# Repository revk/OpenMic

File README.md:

# OpenMic

Now at [Codeberg](https://codeberg.org/RevK/ESP32-OpenMic)

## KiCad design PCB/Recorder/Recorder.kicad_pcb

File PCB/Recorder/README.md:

# Recorder

These files are for use in [KiCad](https://www.kicad.org).

## Trademark

This is an open source project, but bear in mind you cannot sell boards bearing the Andrews & Arnold Ltd name, the A&A logo, the registered trademark AJK logo, or the GS1 allocated EANs assigned to Andrews & Arnold Ltd.

## Images

*Auto generated 2025-08-10T16:03:46*

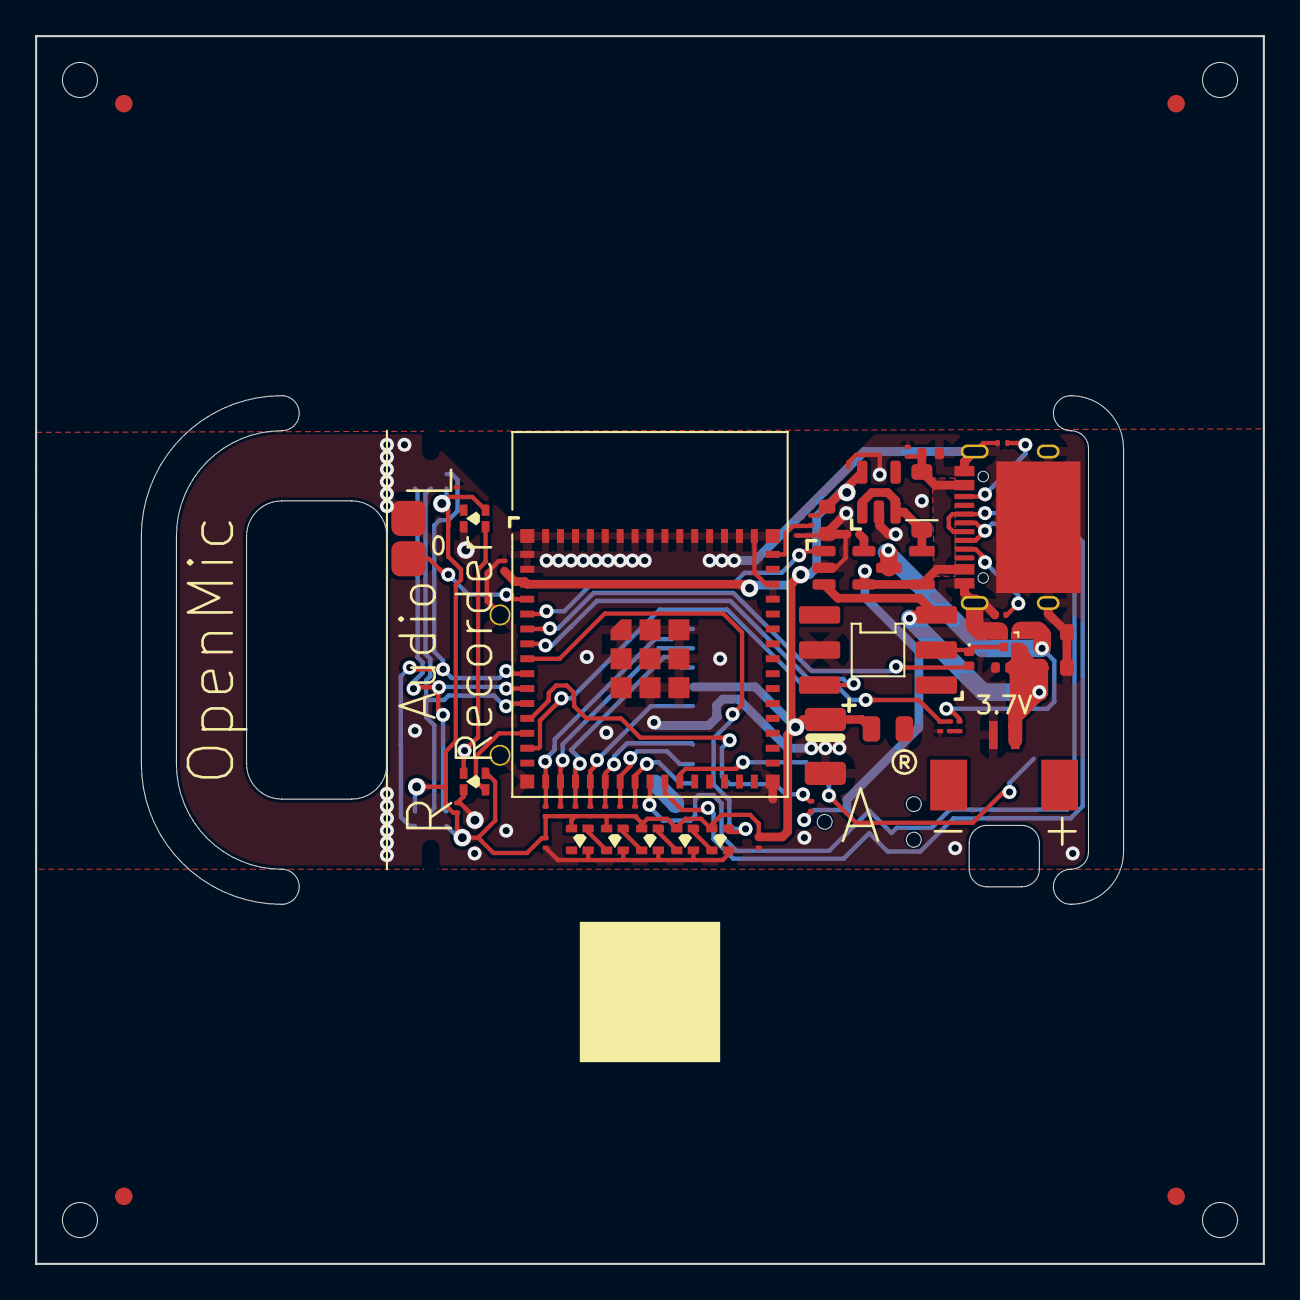
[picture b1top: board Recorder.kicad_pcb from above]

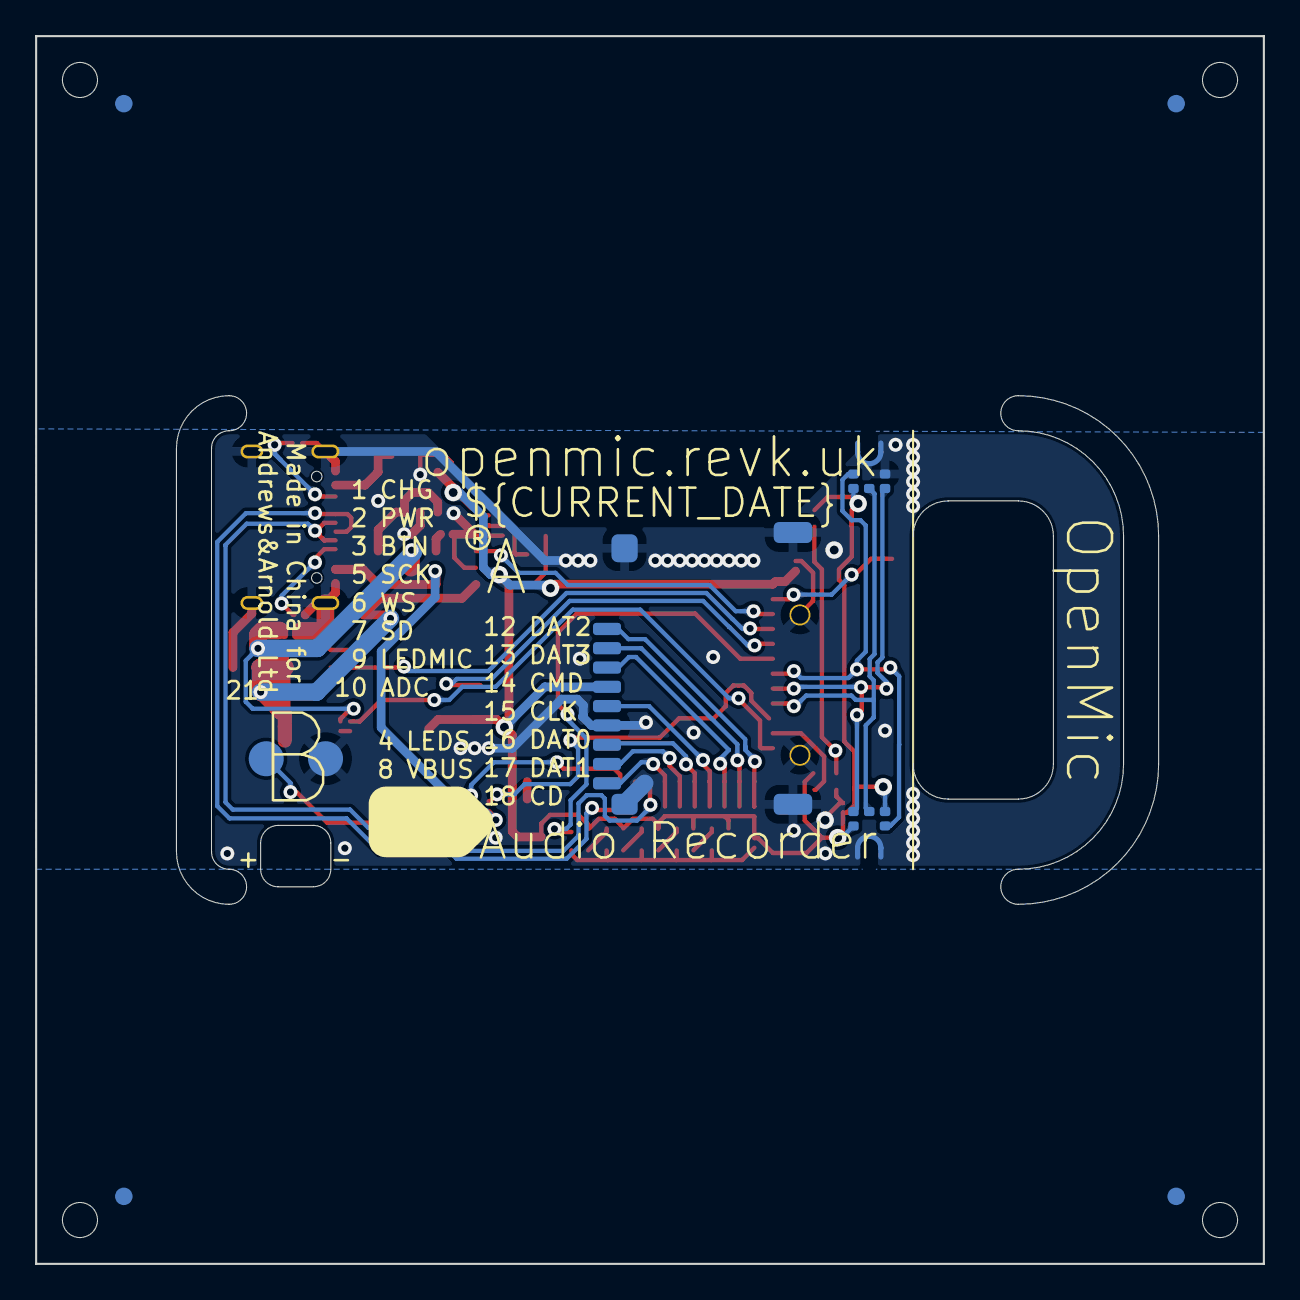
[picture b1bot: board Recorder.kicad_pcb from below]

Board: 2 copper layers, 70.0 x 70.0 mm, 57 parts (7 on the bottom side), 38 nets.

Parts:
BT1: Battery; LiPo1
C1, C3, C5: 22uF; C_0603
C2: 1uF; C_0201
C4, C10, C11, C12, C14: 100nF; C_0201
C6: 220uF Tant; CP_EIA-3528-21_Kemet-B
C7: 10uF 6.3V; C_0402
C9: 100uF; C_0805
D1: D; D_0402
D2: DFN1006-2L
D3: MBR0530; D_SOD-123
D4, D5, D6, D7, D8, D9, D10: XL-1010RGBC-WS2812B; SMD1615
J1: Reset; AA-Pad
J3: TC2030-USB-NL-DS; Tag-Connect_TC2030-IDC-NL_2x03_P1.27mm_Vertical
J4: TF_PUSH
J5: USB-C-Socket-H
J6: Battery; 1.25T-2PWT (Molex 532610271)
PCB1: 70x70; PCB7070
Q1: CJ2301; SOT-23
R1, R2, R3, R4, R5, R6, R7, R9, R10, R11: 10K; R_0201
R8, R12, R13: 5K1; R_0201
R14, R15, R16: 100K 1%; R_0201
SW1: SW_Push_DPDT
TP1, TP2: TestPoint; PAD-2mm
U1: ESP32-S3-MINI-1-N4R2; ESP32-S3-MINI-1
U2: TPS22916CNYFPR; WCSP-4-0.78x0.78
U3: TP4054; SOT-23-5
U4: ME6211C33M5G-N; SOT-23-5-90
U5, U6: ICS-43434; ICS43434_MEMS_Mic_Open
V1, V2: VCUT70N

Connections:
+3V3: C4.1, C5.1, C6.1, C9.1, C10.2, C11.2, C12.1, C14.1, D4.3 (+), D5.3 (+), D6.3 (+), D7.3 (+), D8.3 (+), D9.3 (+), D10.3 (+), J4.4 (VDD), R2.1, R3.1, R4.1, R5.1, R6.1, R7.1, R9.1, R10.1, U1.3 (3V3), U4.5 (OUT), U5.5 (VDD), U6.2 (LR), U6.5 (VDD)
ADC: R15.2, R16.1, U1.14 (GPIO10)
BLINK: D4.2 (I), U1.8 (GPIO4)
BTN: SW1.4 (C), U1.7 (GPIO3)
CHARGING: U1.5 (GPIO1), U3.1 (STAT)
D+: J3.4 (D+), J5.A6 (D+), J5.B6 (D+), U1.24 (GPIO20)
D-: J3.2 (NC), J3.3 (D-), J3.6 (NC), J5.A7 (D-), J5.B7 (D-), U1.23 (GPIO19)
GND: C1.2, C2.2, C3.2, C4.2, C5.2, C6.2, C7.2, C9.2, C10.1, C11.1, C12.2, C14.2, D2.1, D4.1 (-), D5.1 (-), D6.1 (-), D7.1 (-), D8.1 (-), D9.1 (-), D10.1 (-), J1.1, J3.5 (GND), J4.6 (VSS), J4.S (SHIELD), J5.A1 (GND), J5.A12 (GND), J5.B1 (GND), J5.B12 (GND), J5.S1 (SHIELD), J6.2, R8.1, R11.2, R12.2, R13.1, R16.2, SW1.5 (B), TP2.1, U1.1 (GND), U1.2 (GND), U1.42 (GND), U1.43 (GND), U1.46 (GND), U1.47 (GND), U1.48 (GND), U1.49 (GND), U1.50 (GND), U1.51 (GND), U1.52 (GND), U1.53 (GND), U1.54 (GND), U1.55 (GND), U1.56 (GND), U1.57 (GND), U1.58 (GND), U1.59 (GND), U1.60 (GND), U1.61 (GND), U1.62 (GND), U1.63 (GND), U1.64 (GND), U1.65 (GND), U2.B1 (GND), U3.2 (VSS), U4.2 (GND), U5.2 (LR), U5.3 (GND), U6.3 (GND)
LEDMIC: D7.2 (I), U1.13 (GPIO9)
unnamed: D1.1 (K), SW1.2 (B), U2.B2 (ON)
unnamed: D3.1 (K), Q1.2 (S), U4.1 (IN), U4.3 (EN)
unnamed: D4.4 (O), D5.2 (I)
unnamed: D5.4 (O), D6.2 (I)
unnamed: D6.4 (O), D8.2 (I)
unnamed: D7.4 (O), D9.2 (I)
unnamed: D8.4 (O), D10.2 (I)
unnamed: J1.2, U1.25 (GPIO21)
unnamed: J5.A5 (CC1), R12.1
unnamed: J5.B5 (CC2), R13.2
unnamed: R14.2, R15.1
unnamed: C2.1, R2.2, U1.45 (EN)
unnamed: TP1.1, U1.4 (GPIO0)
unnamed: R1.1, U1.12 (GPIO8)
unnamed: R8.2, U3.5 (PROG)
PWR: D1.2 (A), U1.6 (GPIO2)
SCK: U1.9 (GPIO5), U5.4 (SCK), U6.4 (SCK)
SD: U1.11 (GPIO7), U5.6 (SD), U6.6 (SD)
SDCD: J4.9 (CD), R3.2, U1.22 (GPIO18)
SDCLK: J4.5 (CLK), R6.2, U1.19 (GPIO15)
SDCMD: J4.3 (CMD), R7.2, U1.18 (GPIO14)
SDDAT0: J4.7 (DAT0), R5.2, U1.20 (GPIO16)
SDDAT1: J4.8 (DAT1), R4.2, U1.21 (GPIO17)
SDDAT2: J4.1 (DAT2), R10.2, U1.16 (GPIO12)
SDDAT3: J4.2 (DAT3/CD), R9.2, U1.17 (GPIO13)
VBATCHG: C1.1, D2.2, J6.1, SW1.3 (C), U2.A2 (VIN), U3.3 (VBAT)
VBUS: C7.1, D3.2 (A), J3.1 (VBUS), J5.A4 (VBUS), J5.A9 (VBUS), J5.B4 (VBUS), J5.B9 (VBUS), Q1.1 (G), R1.2, R11.1, U3.4 (VDD)
VSWITCHED: C3.1, Q1.3 (D), R14.1, U2.A1 (VOUT)
WS: U1.10 (GPIO6), U5.1 (WS), U6.1 (WS)

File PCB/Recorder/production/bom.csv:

Designator,Footprint,Quantity,Value,LCSC Part #
"C1, C3, C5",C_0603,3,22uF,
"C10, C11, C12, C14, C4",C_0201,5,100nF,
C2,C_0201,1,1uF,
C6,CP_EIA-3528-21_Kemet-B,1,220uF Tant,C122649
C7,C_0402,1,10uF 6.3V,C15525
C9,C_0805,1,100uF,C141660
D1,D_0402,1,D,C28642302
"D10, D4, D5, D6, D7, D8, D9",SMD1615,7,XL-1010RGBC-WS2812B,C5349954
D2,DFN1006-2L,1,~,C5137770
D3,D_SOD-123,1,MBR0530,C5204746
J4,TF_PUSH,1,TF_PUSH,C393941
J5,USB-C-Socket-H,1,USB-C-Socket-H,C709357
J6,1.25T-2PWT (Molex 532610271),1,Battery,C177225
Q1,SOT-23,1,CJ2301,C8547
"R1, R10, R11, R2, R3, R4, R5, R6, R7, R9",R_0201,10,10K,C106225
"R12, R13, R8",R_0201,3,5K1,C274341
"R14, R15, R16",R_0201,3,100K 1%,C717003
SW1,SW_Push_DPDT,1,SW_Push_DPDT,C2911139
U1,ESP32-S3-MINI-1,1,ESP32-S3-MINI-1-N4R2,C3013941
U2,WCSP-4-0.78x0.78,1,TPS22916CNYFPR,C2655476
U3,SOT-23-5,1,TP4054,C668215
U4,SOT-23-5-90,1,ME6211C33M5G-N,
"U5, U6",ICS43434_MEMS_Mic_Open,2,ICS-43434,C5656610

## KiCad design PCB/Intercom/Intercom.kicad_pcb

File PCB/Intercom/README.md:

# Intercom

These files are for use in [KiCad](https://www.kicad.org).

## Trademark

This is an open source project, but bear in mind you cannot sell boards bearing the Andrews & Arnold Ltd name, the A&A logo, the registered trademark AJK logo, or the GS1 allocated EANs assigned to Andrews & Arnold Ltd.

## Images

*Auto generated 2025-08-10T15:43:51*

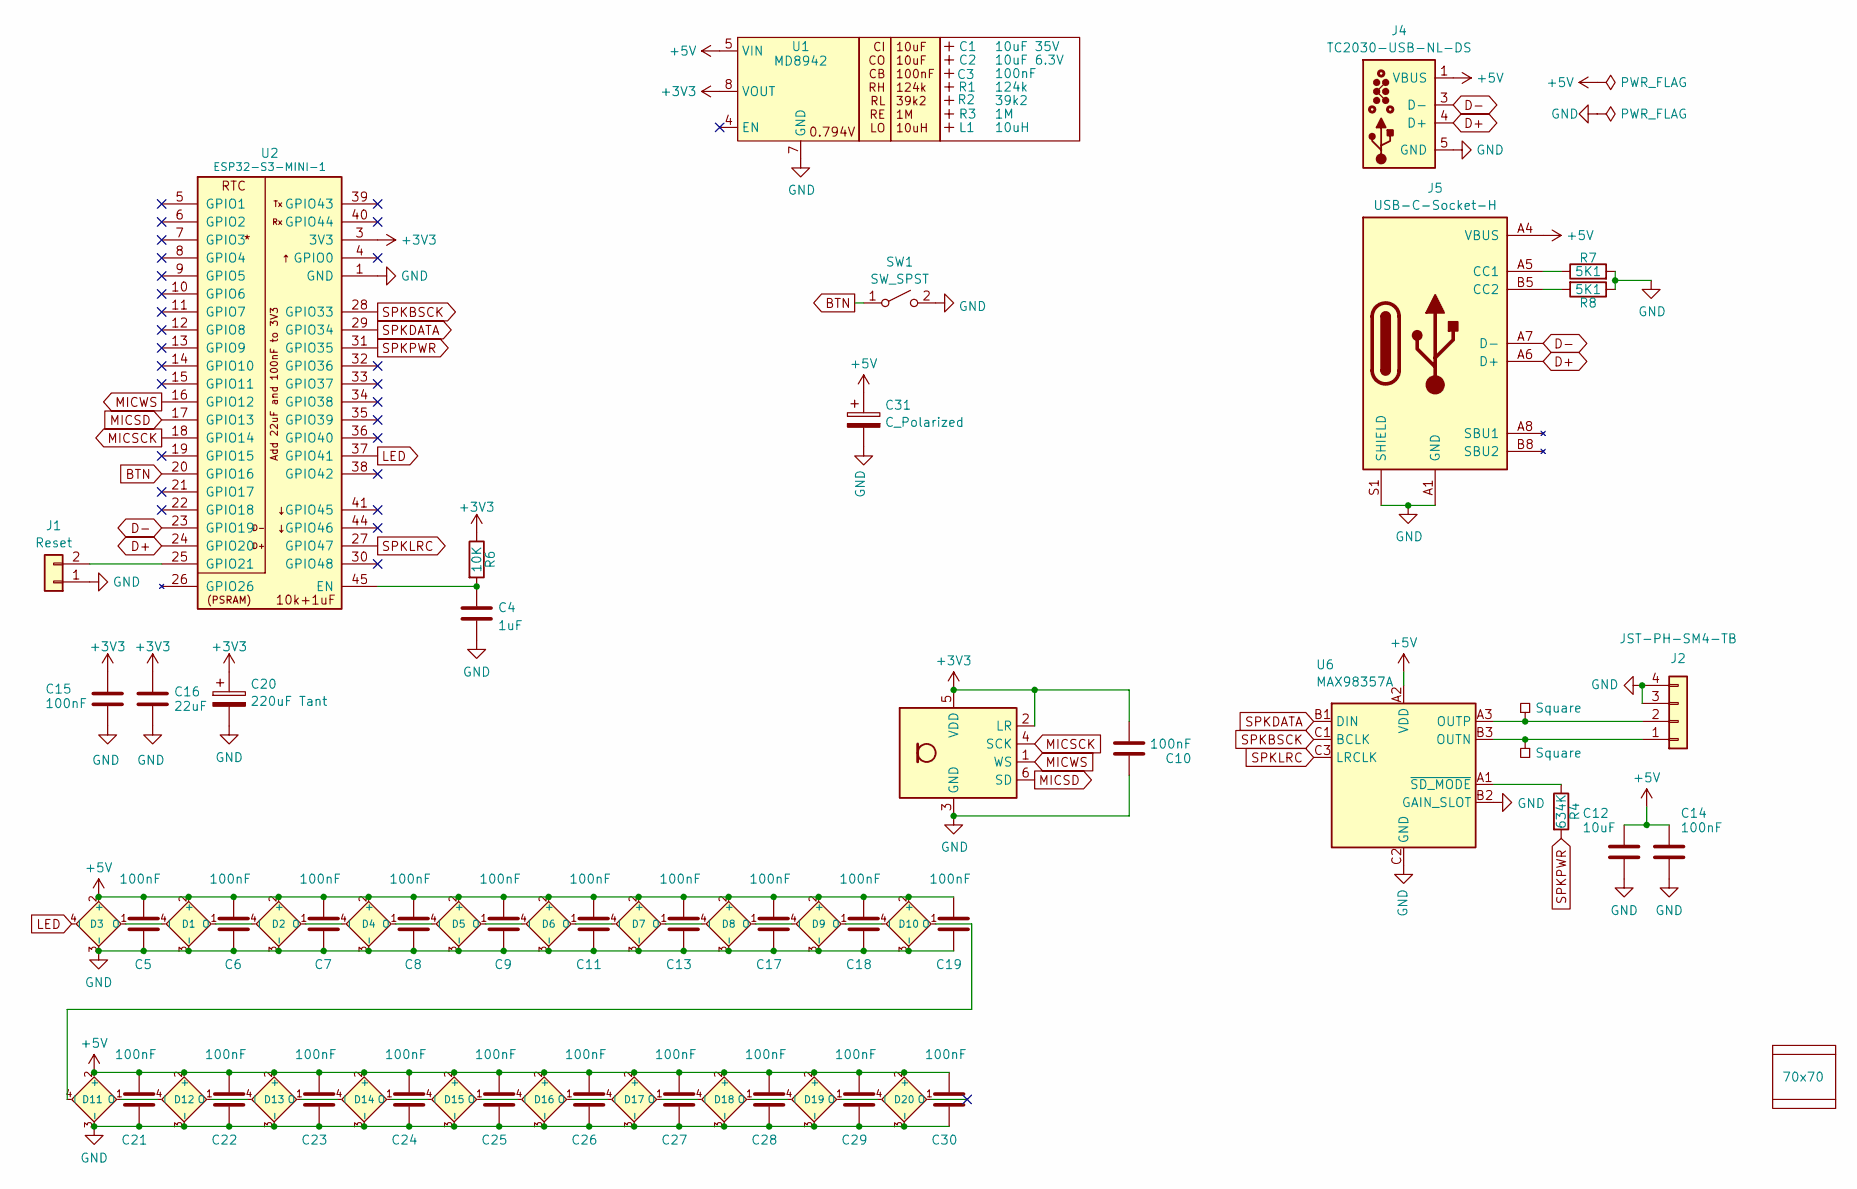
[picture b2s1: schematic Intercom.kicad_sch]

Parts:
C1: 10uF 35V; C_0603_; MPN C194427
C2: 10uF 6.3V; C_0603_; MPN C1691
C3: 100nF; C_0603_
C4: 1uF; C_0402
C5, C6, C7, C8, C9, C10, C11, C13, C14, C15, C17, C18, C19, C21, C22, C23, C24, C25, C26, C27, C28, C29, C30: 100nF; C_0402
C12: 10uF; C_0402; MPN C15525
C16: 22uF; C_0603
C20: 220uF Tant; CP_EIA-3528-21_Kemet-B; MPN C122649
C31: C_Polarized; CP_EIA-7343-31_Kemet-D; MPN C106188
D1, D2, D3, D4, D5, D6, D7, D8, D9, D10, D11, D12, D13, D14, D15, D16, D17, D18, D19, D20: XL-1010RGBC-WS2812B; SMD1010; MPN C5349953
J1: Reset; AA-Pad
J2: JST-PH-SM4-TB; JST_PH_S2B-PH-SM4-TB_1x02-1MP_P2.00mm_Horizontal; MPN C295747
J4: TC2030-USB-NL-DS; Tag-Connect_TC2030-IDC-NL_2x03_P1.27mm_Vertical
J5: USB-C-Socket-H; MPN C709357
L1: 10uH; L_4x4_
P1, P2: Square; PAD-2mm
PCB1: 70x70; PCB7070
R1: 124k; R_0402_
R2: 39k2; R_0402_
R3: 1M; R_0402_
R4: 634K; R_0402
R6: 10K; R_0402
R7, R8: 5K1; R_0402
SW1: SW_SPST; SW_Push_1TS009xxxx-xxxx-xxxx_6x6x5mm; MPN C390925
U1: MD8942; SOT-23-6-MD8942; MPN C2684786
U2: ESP32-S3-MINI-1; MPN C3013941
U4: ICS43434; ICS43434_MEMS_Mic_Open; MPN C5656610
U6: MAX98357A; WLP-1.437mmx1.347mm-0.21mm-ball; MPN C2682619
V2, V3: VCUT70N

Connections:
+3V3: C10.2, C15.1, C16.1, C20.1, R6.1, U1.8 (VOUT), U2.3 (3V3), U4.2 (LR), U4.5 (VDD)
+5V: C5.2, C6.2, C7.2, C8.2, C9.2, C11.2, C12.1, C13.2, C14.1, C17.2, C18.2, C19.2, C21.2, C22.2, C23.2, C24.2, C25.2, C26.2, C27.2, C28.2, C29.2, C30.2, C31.1, D1.2 (+), D2.2 (+), D3.2 (+), D4.2 (+), D5.2 (+), D6.2 (+), D7.2 (+), D8.2 (+), D9.2 (+), D10.2 (+), D11.2 (+), D12.2 (+), D13.2 (+), D14.2 (+), D15.2 (+), D16.2 (+), D17.2 (+), D18.2 (+), D19.2 (+), D20.2 (+), J4.1 (VBUS), J5.A4 (VBUS), J5.A9 (VBUS), J5.B4 (VBUS), J5.B9 (VBUS), U1.5 (VIN), U6.A2 (VDD)
BTN: SW1.1 (A), U2.20 (GPIO16)
D+: J4.4 (D+), J5.A6 (D+), J5.B6 (D+), U2.24 (GPIO20)
D-: J4.2 (NC), J4.3 (D-), J4.6 (NC), J5.A7 (D-), J5.B7 (D-), U2.23 (GPIO19)
GND: C4.2, C5.1, C6.1, C7.1, C8.1, C9.1, C10.1, C11.1, C12.2, C13.1, C14.2, C15.2, C16.2, C17.1, C18.1, C19.1, C20.2, C21.1, C22.1, C23.1, C24.1, C25.1, C26.1, C27.1, C28.1, C29.1, C30.1, C31.2, D1.3 (-), D2.3 (-), D3.3 (-), D4.3 (-), D5.3 (-), D6.3 (-), D7.3 (-), D8.3 (-), D9.3 (-), D10.3 (-), D11.3 (-), D12.3 (-), D13.3 (-), D14.3 (-), D15.3 (-), D16.3 (-), D17.3 (-), D18.3 (-), D19.3 (-), D20.3 (-), J1.1, J2.3, J2.4, J4.5 (GND), J5.A1 (GND), J5.A12 (GND), J5.B1 (GND), J5.B12 (GND), J5.S1 (SHIELD), R7.2, R8.1, SW1.2 (B), U1.2 (GND), U1.7 (GND), U2.1 (GND), U2.2 (GND), U2.42 (GND), U2.43 (GND), U2.46 (GND), U2.47 (GND), U2.48 (GND), U2.49 (GND), U2.50 (GND), U2.51 (GND), U2.52 (GND), U2.53 (GND), U2.54 (GND), U2.55 (GND), U2.56 (GND), U2.57 (GND), U2.58 (GND), U2.59 (GND), U2.60 (GND), U2.61 (GND), U2.62 (GND), U2.63 (GND), U2.64 (GND), U2.65 (GND), U4.3 (GND), U6.B2 (GAIN_SLOT), U6.C2 (GND)
LED: D3.4 (I), U2.37 (GPIO41)
MICSCK: U2.18 (GPIO14), U4.4 (SCK)
MICSD: U2.17 (GPIO13), U4.6 (SD)
MICWS: U2.16 (GPIO12), U4.1 (WS)
unnamed: D1.4 (I), D3.1 (O)
unnamed: D1.1 (O), D2.4 (I)
unnamed: D2.1 (O), D4.4 (I)
unnamed: D4.1 (O), D5.4 (I)
unnamed: D5.1 (O), D6.4 (I)
unnamed: D6.1 (O), D7.4 (I)
unnamed: D7.1 (O), D8.4 (I)
unnamed: D8.1 (O), D9.4 (I)
unnamed: D9.1 (O), D10.4 (I)
unnamed: D10.1 (O), D11.4 (I)
unnamed: D11.1 (O), D12.4 (I)
unnamed: D12.1 (O), D13.4 (I)
unnamed: D13.1 (O), D14.4 (I)
unnamed: D14.1 (O), D15.4 (I)
unnamed: D15.1 (O), D16.4 (I)
unnamed: D16.1 (O), D17.4 (I)
unnamed: D17.1 (O), D18.4 (I)
unnamed: D18.1 (O), D19.4 (I)
unnamed: D19.1 (O), D20.4 (I)
unnamed: J1.2, U2.25 (GPIO21)
unnamed: J2.1, P2.1, U6.B3 (OUTN)
unnamed: J2.2, P1.1, U6.A3 (OUTP)
unnamed: J5.A5 (CC1), R7.1
unnamed: J5.B5 (CC2), R8.2
unnamed: C4.1, R6.2, U2.45 (EN)
unnamed: R4.1, U6.A1 (~SD_MODE)
SPKBSCK: U2.28 (GPIO33), U6.C1 (BCLK)
SPKDATA: U2.29 (GPIO34), U6.B1 (DIN)
SPKLRC: U2.27 (GPIO47), U6.C3 (LRCLK)
SPKPWR: R4.2, U2.31 (GPIO35)

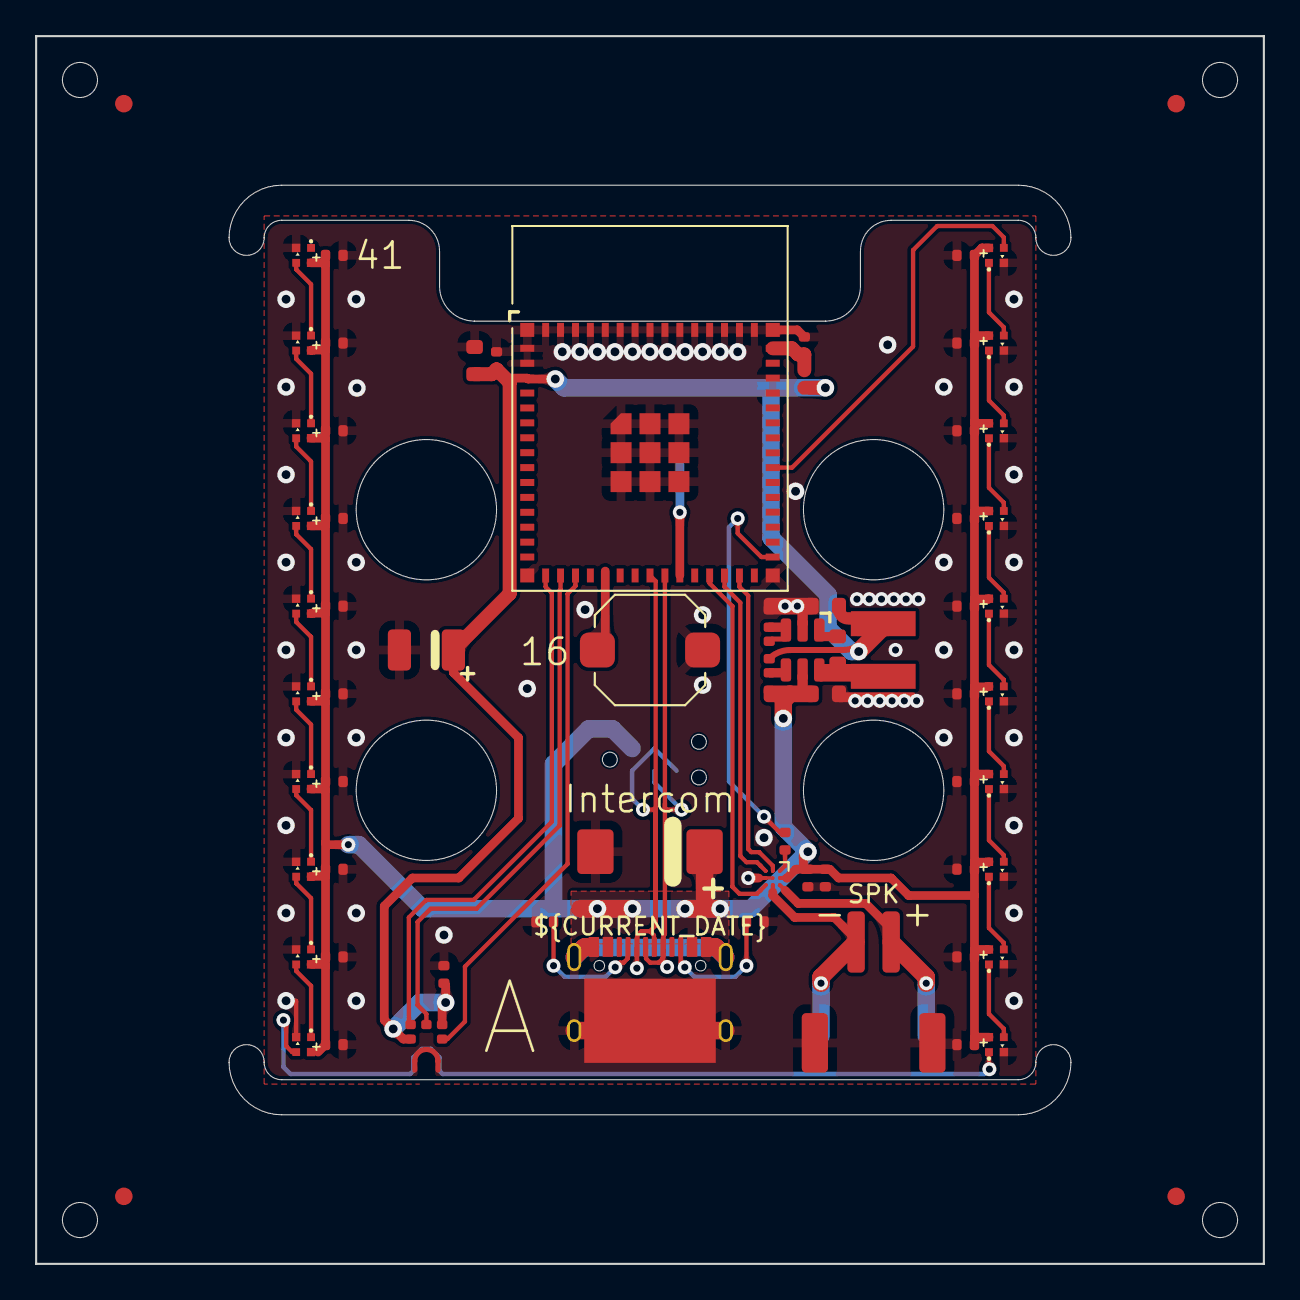
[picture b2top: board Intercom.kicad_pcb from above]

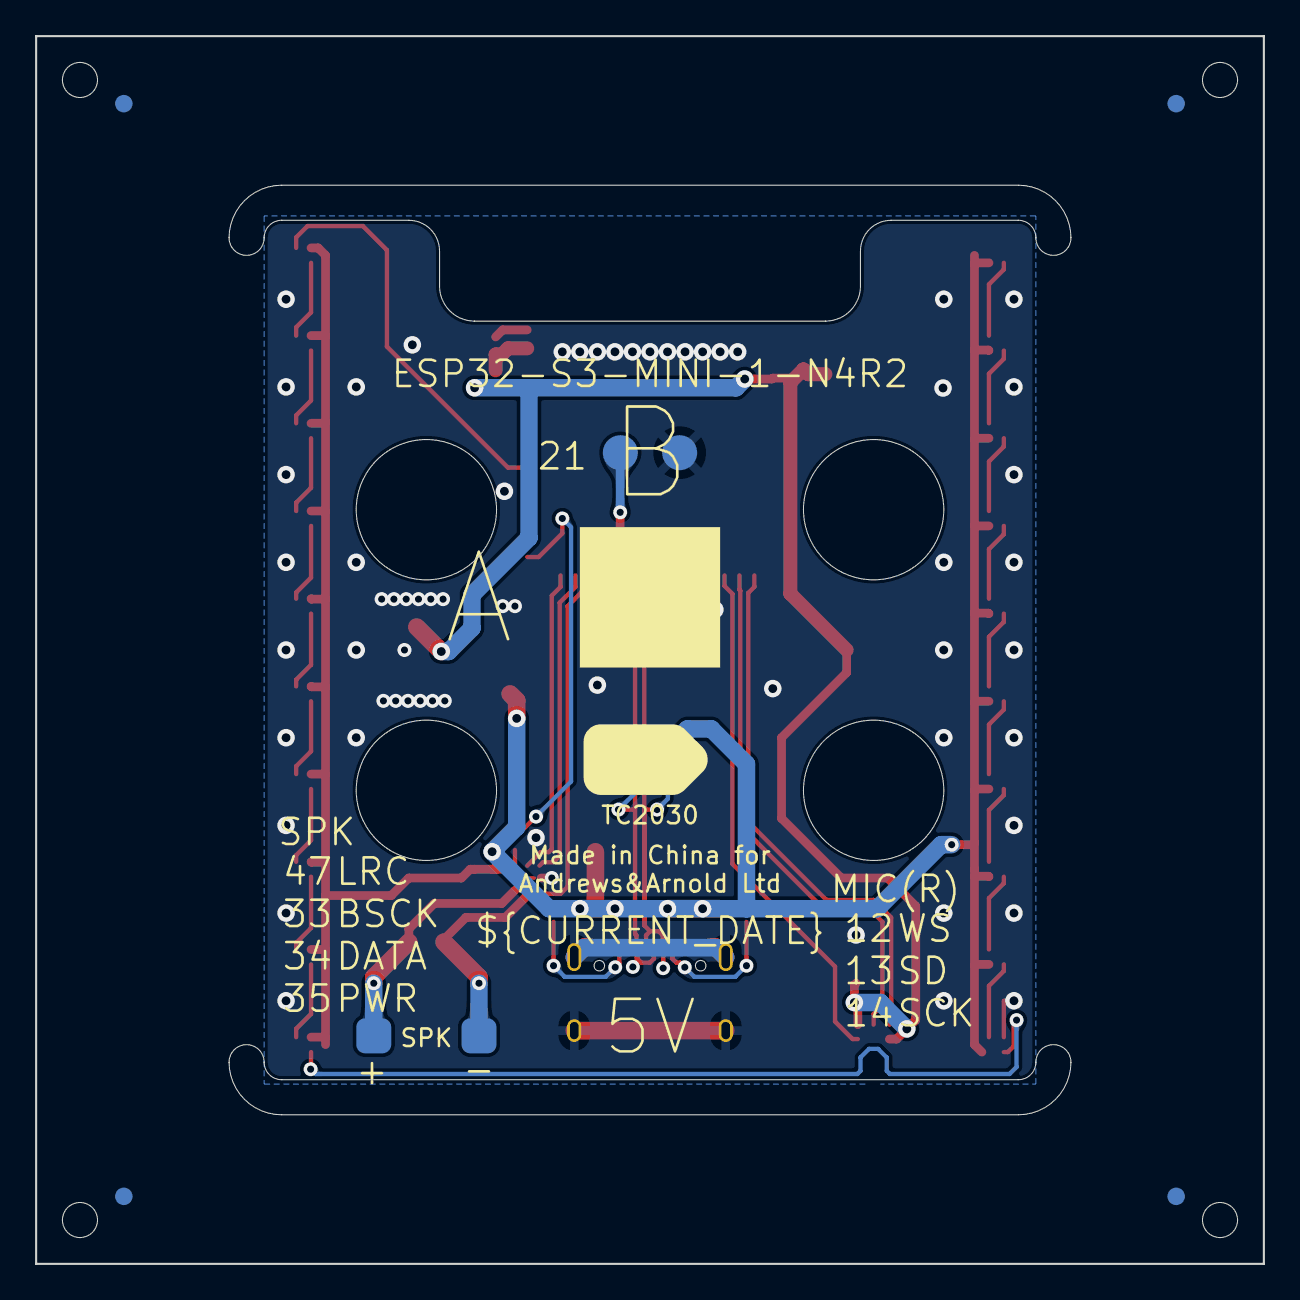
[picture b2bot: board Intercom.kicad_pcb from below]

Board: 2 copper layers, 70.0 x 70.0 mm, 73 parts (4 on the bottom side), 40 nets.

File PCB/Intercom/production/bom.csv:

Designator,Footprint,Quantity,Value,LCSC Part #
C1,C_0603_,1,10uF 35V,C194427
"C10, C11, C13, C14, C15, C17, C18, C19, C21, C22, C23, C24, C25, C26, C27, C28, C29, C30, C5, C6, C7, C8, C9",C_0402,23,100nF,
C12,C_0402,1,10uF,C15525
C16,C_0603,1,22uF,
C2,C_0603_,1,10uF 6.3V,C1691
C20,CP_EIA-3528-21_Kemet-B,1,220uF Tant,C122649
C3,C_0603_,1,100nF,
C31,CP_EIA-7343-31_Kemet-D,1,C_Polarized,C106188
C4,C_0402,1,1uF,
"D1, D10, D11, D12, D13, D14, D15, D16, D17, D18, D19, D2, D20, D3, D4, D5, D6, D7, D8, D9",SMD1010,20,XL-1010RGBC-WS2812B,C5349953
J2,JST_PH_S2B-PH-SM4-TB_1x02-1MP_P2.00mm_Horizontal,1,JST-PH-SM4-TB,C295747
J5,USB-C-Socket-H,1,USB-C-Socket-H,C709357
L1,L_4x4_,1,10uH,
R1,R_0402_,1,124k,
R2,R_0402_,1,39k2,
R3,R_0402_,1,1M,
R4,R_0402,1,634K,
R6,R_0402,1,10K,
"R7, R8",R_0402,2,5K1,
SW1,SW_Push_1TS009xxxx-xxxx-xxxx_6x6x5mm,1,SW_SPST,C390925
U1,SOT-23-6-MD8942,1,MD8942,C2684786
U2,ESP32-S3-MINI-1,1,ESP32-S3-MINI-1,C3013941
U4,ICS43434_MEMS_Mic_Open,1,ICS43434,C5656610
U6,WLP-1.437mmx1.347mm-0.21mm-ball,1,MAX98357A,C2682619

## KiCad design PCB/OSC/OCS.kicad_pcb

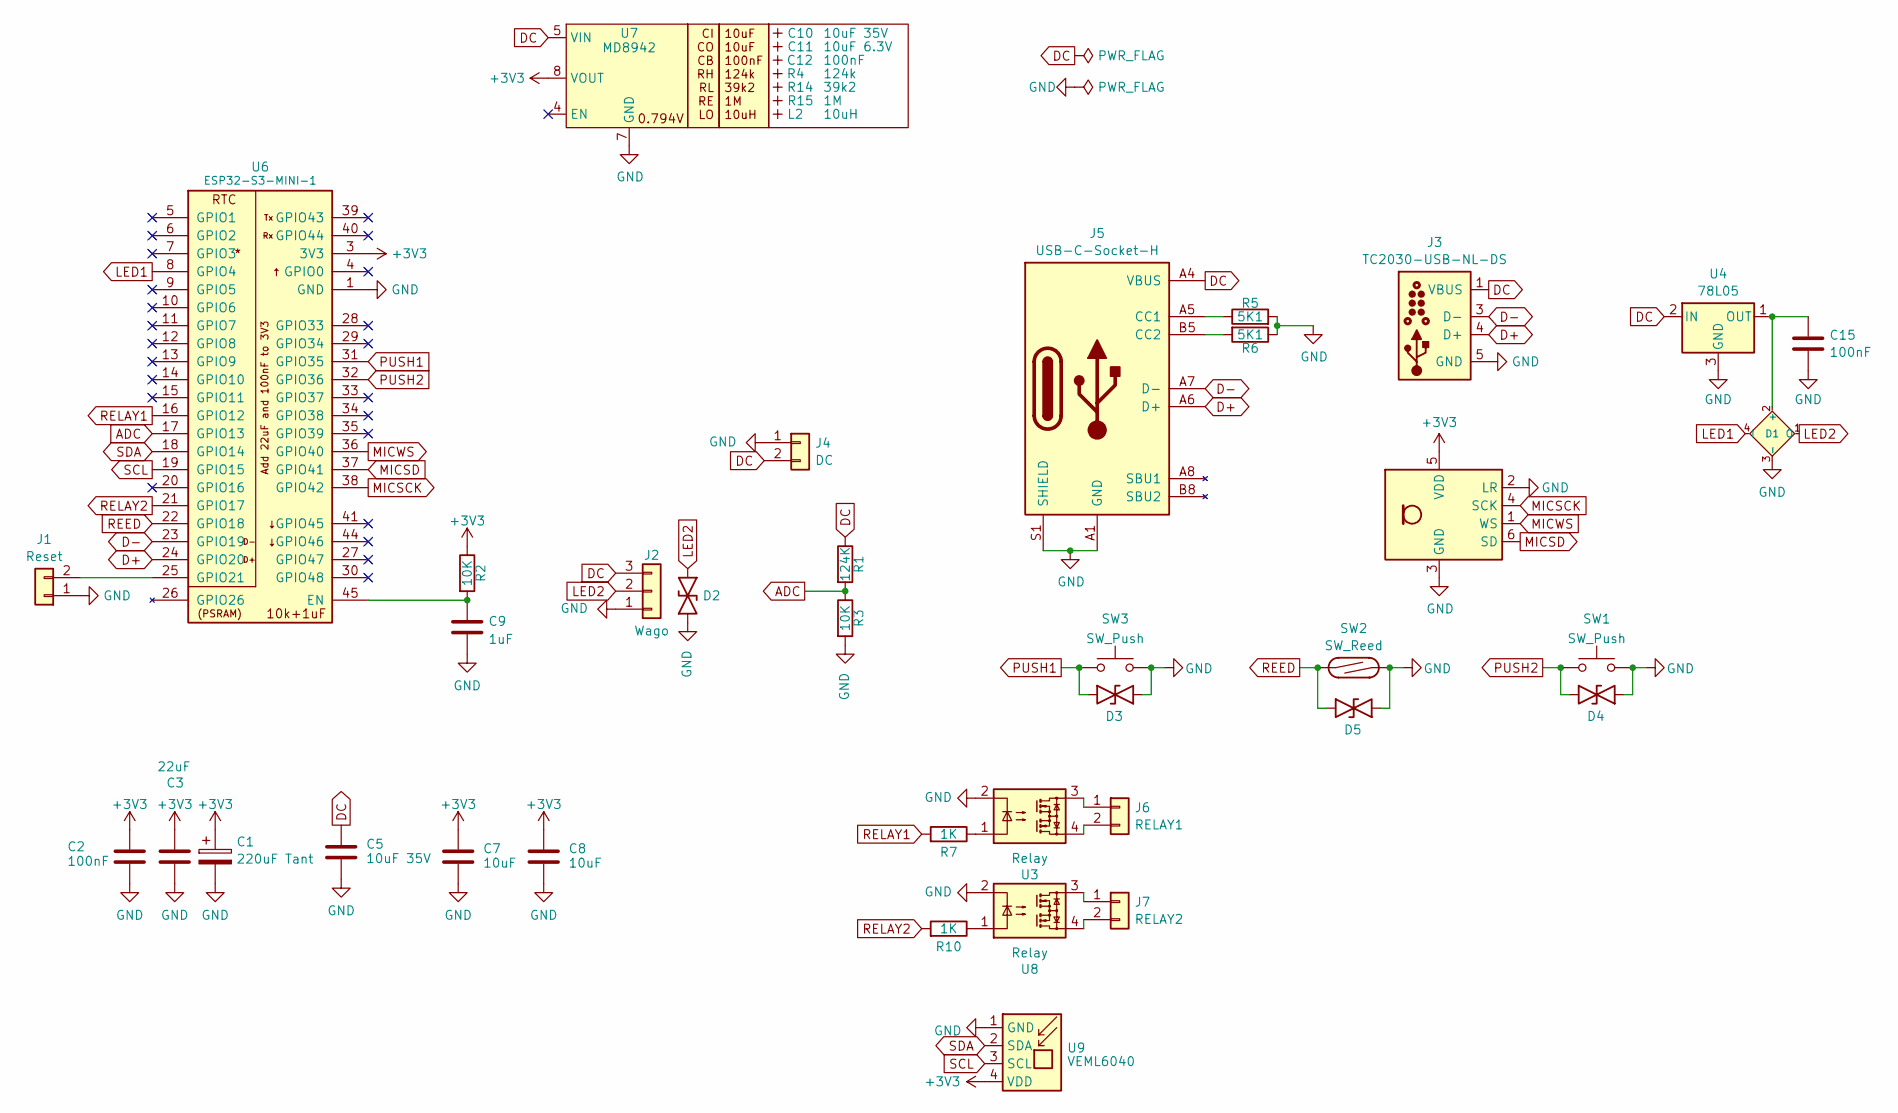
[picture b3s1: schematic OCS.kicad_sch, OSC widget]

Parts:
C1: 220uF Tant
C2, C12, C15: 100nF
C3: 22uF
C5, C10: 10uF 35V
C7, C8: 10uF
C9: 1uF
C11: 10uF 6.3V
D1: XL-1010RGBC-WS2812B; MPN C5349953
D2, D3, D4, D5: DFN1006-2L; MPN C5137770
J1: Reset
J2: Wago
J3: TC2030-USB-NL-DS; Tag-Connect_TC2030-IDC-NL_2x03_P1.27mm_Vertical
J4: DC
J5: USB-C-Socket-H; MPN C709357
J6: RELAY1
J7: RELAY2
L2: 10uH
R1: 124K
R2, R3: 10K
R4: 124k
R5, R6: 5K1
R7, R10: 1K
R14: 39k2
R15: 1M
SW1, SW3: SW_Push
SW2: SW_Reed
U1: ICS43434_MEMS_Mic; MPN C5656610
U3, U8: Relay; SO-4_4.4x4.3mm_P2.54mm
U4: 78L05; SOT-23; MPN C22392284
U6: ESP32-S3-MINI-1; MPN C3013941
U7: MD8942; SOT-23-6-MD8942; MPN C2684786
U9: VEML6040; MPN C78465

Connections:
+3V3: C1.1, C2.1, C3.1, C7.1, C8.1, R2.1, U1.5 (VDD), U6.3 (3V3), U7.8 (VOUT), U9.4 (VDD)
ADC: R1.2, R3.1, U6.17 (GPIO13)
D+: J3.4 (D+), J5.A6 (D+), J5.B6 (D+), U6.24 (GPIO20)
D-: J3.3 (D-), J5.A7 (D-), J5.B7 (D-), U6.23 (GPIO19)
DC: C5.1, J2.3, J3.1 (VBUS), J3.2 (VBUS), J4.2, J5.A4 (VBUS), J5.A9 (VBUS), J5.B4 (VBUS), J5.B9 (VBUS), R1.1, U4.2 (IN), U7.5 (VIN)
GND: C1.2, C2.2, C3.2, C5.2, C7.2, C8.2, C9.2, C15.2, D1.3 (-), D2.1, D3.1, D4.1, D5.1, J1.1, J2.1, J3.5 (GND), J3.6 (GND), J4.1, J5.A1 (GND), J5.A12 (GND), J5.B1 (GND), J5.B12 (GND), J5.S1 (SHIELD), R3.2, R5.2, R6.1, SW1.1, SW2.2, SW3.1, U1.2 (LR), U1.3 (GND), U3.2, U4.3 (GND), U6.1 (GND), U6.2 (GND), U6.42 (GND), U6.43 (GND), U6.46 (GND), U6.47 (GND), U6.48 (GND), U6.49 (GND), U6.50 (GND), U6.51 (GND), U6.52 (GND), U6.53 (GND), U6.54 (GND), U6.55 (GND), U6.56 (GND), U6.57 (GND), U6.58 (GND), U6.59 (GND), U6.60 (GND), U6.61 (GND), U6.62 (GND), U6.63 (GND), U6.64 (GND), U6.65 (GND), U7.2 (GND), U7.7 (GND), U8.2, U9.1 (GND)
LED1: D1.4 (I), U6.8 (GPIO4)
LED2: D1.1 (O), D2.2, J2.2
MICSCK: U1.4 (SCK), U6.38 (GPIO42)
MICSD: U1.6 (SD), U6.37 (GPIO41)
MICWS: U1.1 (WS), U6.36 (GPIO40)
unnamed: C15.1, D1.2 (+), U4.1 (OUT)
unnamed: J1.2, U6.25 (GPIO21)
unnamed: J5.A5 (CC1), R5.1
unnamed: J5.B5 (CC2), R6.2
unnamed: J6.1, U3.3
unnamed: J6.2, U3.4
unnamed: J7.1, U8.3
unnamed: J7.2, U8.4
unnamed: R7.1, U3.1
unnamed: R10.1, U8.1
unnamed: C9.1, R2.2, U6.45 (EN)
PUSH1: D3.2, SW3.2, U6.31 (GPIO35)
PUSH2: D4.2, SW1.2, U6.32 (GPIO36)
REED: D5.2, SW2.1, U6.22 (GPIO18)
RELAY1: R7.2, U6.16 (GPIO12)
RELAY2: R10.2, U6.21 (GPIO17)
SCL: U6.19 (GPIO15), U9.3 (SCL)
SDA: U6.18 (GPIO14), U9.2 (SDA)

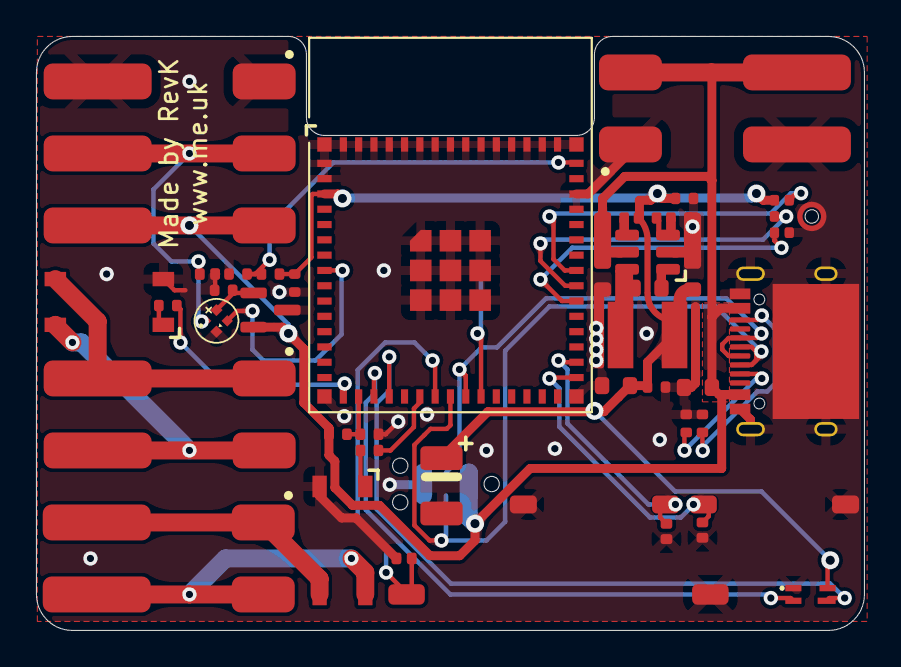
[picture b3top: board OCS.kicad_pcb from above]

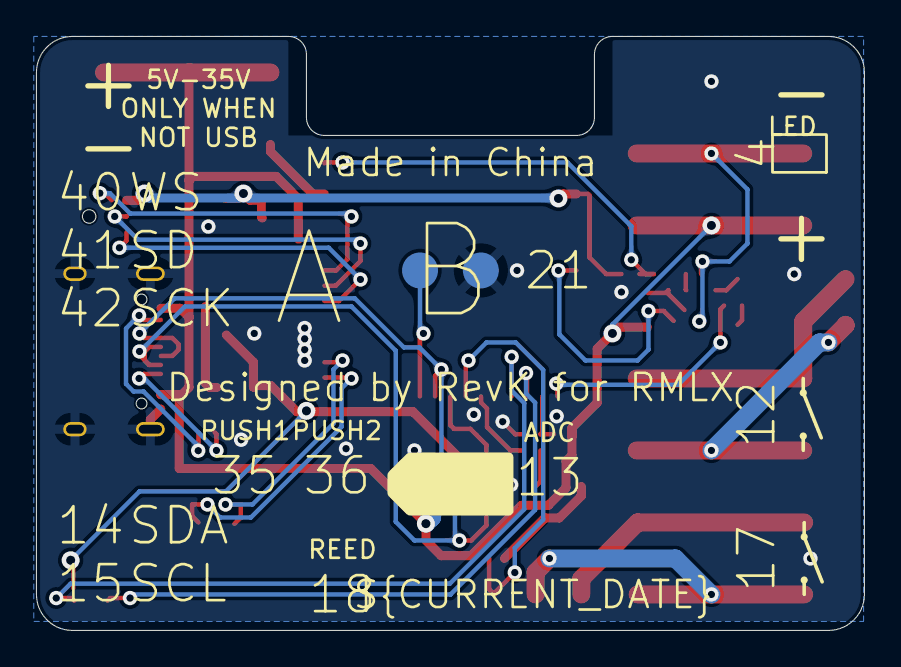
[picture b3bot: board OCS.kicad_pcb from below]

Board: 4 copper layers, 46.0 x 33.0 mm, 44 parts (2 on the bottom side), 29 nets.
